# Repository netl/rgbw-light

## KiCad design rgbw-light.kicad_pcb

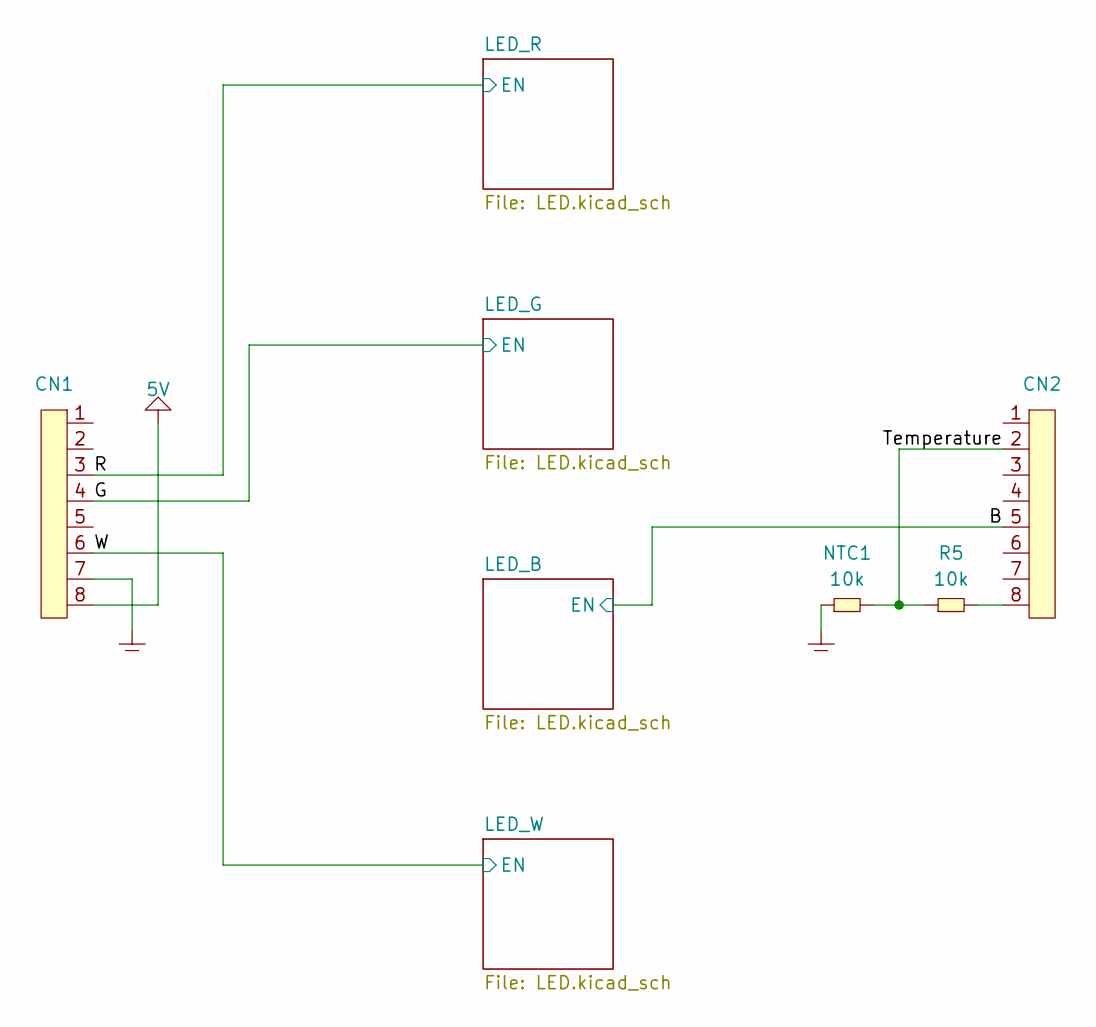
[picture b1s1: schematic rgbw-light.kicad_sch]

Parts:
CN1, CN2: 1x8
NTC1: 10k; 0603
R5: 10k; 0603

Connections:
5V: CN1.8; also elsewhere on the board
/B: CN2.5; also elsewhere on the board
/G: CN1.4; also elsewhere on the board
/R: CN1.3; also elsewhere on the board
/Temperature: CN2.2, NTC1.2, R5.1
/W: CN1.6; also elsewhere on the board
GND: CN1.7, NTC1.1; also elsewhere on the board
unnamed: CN2.8, R5.2

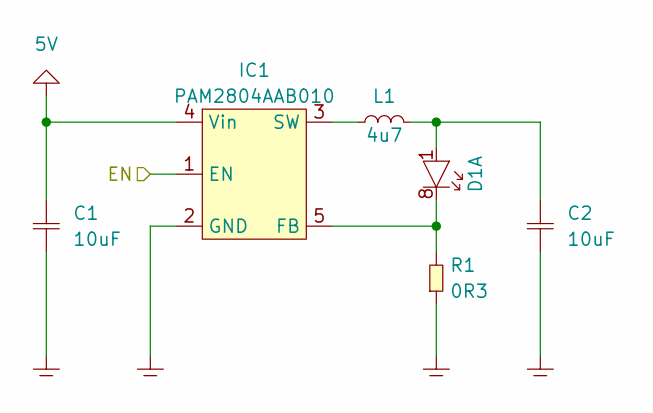
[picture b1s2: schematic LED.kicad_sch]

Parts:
C1, C2: 10uF; 0805
D1: QLSP06RGBXWAJ; 3030_8; MPN QLSP06RGBXWAJ; Digi-Key 3970-QLSP06RGBXWAJCT-ND
IC1: PAM2804AAB010; SOT-23-5; MPN PAM2804AAB010; Digi-Key PAM2804AAB010DICT-ND
L1: 4u7; CDRH2D11
R1: 0R3; 0603

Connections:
5V: C1.1, IC1.4 (Vin); also elsewhere on the board
/R: IC1.1 (EN); also elsewhere on the board
GND: C1.2, C2.2, IC1.2 (GND), R1.1; also elsewhere on the board
unnamed: C2.1, D1.1 (A), L1.2
unnamed: D1.8 (K), IC1.5 (FB), R1.2
unnamed 10: D1.2 (A); also elsewhere on the board
unnamed 11: D1.7 (K); also elsewhere on the board
unnamed 12: D1.3 (A); also elsewhere on the board
unnamed 13: D1.6 (K); also elsewhere on the board
unnamed 14: D1.4 (A); also elsewhere on the board
unnamed 15: D1.5 (K); also elsewhere on the board
unnamed: IC1.3 (SW), L1.1

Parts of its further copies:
C3, C4, C5, C6, C7, C8: 10uF; 0805
IC2, IC3, IC4: PAM2804AAB010; SOT-23-5; MPN PAM2804AAB010; Digi-Key PAM2804AAB010DICT-ND
L2, L3, L4: 4u7; CDRH2D11
R2, R3, R4: 0R3; 0603

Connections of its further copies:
5V: C3.1, C5.1, C7.1, IC2.4 (Vin), IC3.4 (Vin), IC4.4 (Vin); also elsewhere on the board
/B: IC3.1 (EN); also elsewhere on the board
/G: IC2.1 (EN); also elsewhere on the board
/W: IC4.1 (EN); also elsewhere on the board
GND: C3.2, C4.2, C5.2, C6.2, C7.2, C8.2, IC2.2 (GND), IC3.2 (GND), IC4.2 (GND), R2.1, R3.1, R4.1; also elsewhere on the board
unnamed 10: C4.1, L2.2; also elsewhere on the board
unnamed 11: IC2.5 (FB), R2.2; also elsewhere on the board
unnamed 12: C6.1, L3.2; also elsewhere on the board
unnamed 13: IC3.5 (FB), R3.2; also elsewhere on the board
unnamed 14: C8.1, L4.2; also elsewhere on the board
unnamed 15: IC4.5 (FB), R4.2; also elsewhere on the board
unnamed: IC2.3 (SW), L2.1
unnamed: IC3.3 (SW), L3.1
unnamed: IC4.3 (SW), L4.1

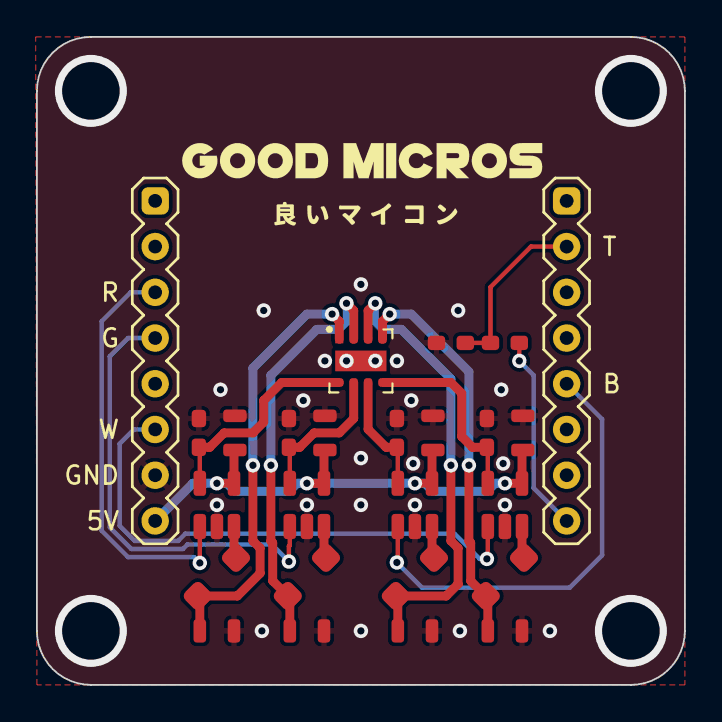
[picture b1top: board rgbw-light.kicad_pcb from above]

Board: 2 copper layers, 36.0 x 36.0 mm, 25 parts (0 on the bottom side), 20 nets.

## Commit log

2023-03-01 created schematic, layout
2023-03-02 added connector, mounting holes. completed layout
2023-03-02 minor cleanup. generated outputs
2024-03-19 changed layout to match d1 mini
2024-03-19 fixed 5V and GND being reversed on silkscreen
2024-03-19 saved layout...
2025-04-04 moved blue from FLASH pin to GPIO12
